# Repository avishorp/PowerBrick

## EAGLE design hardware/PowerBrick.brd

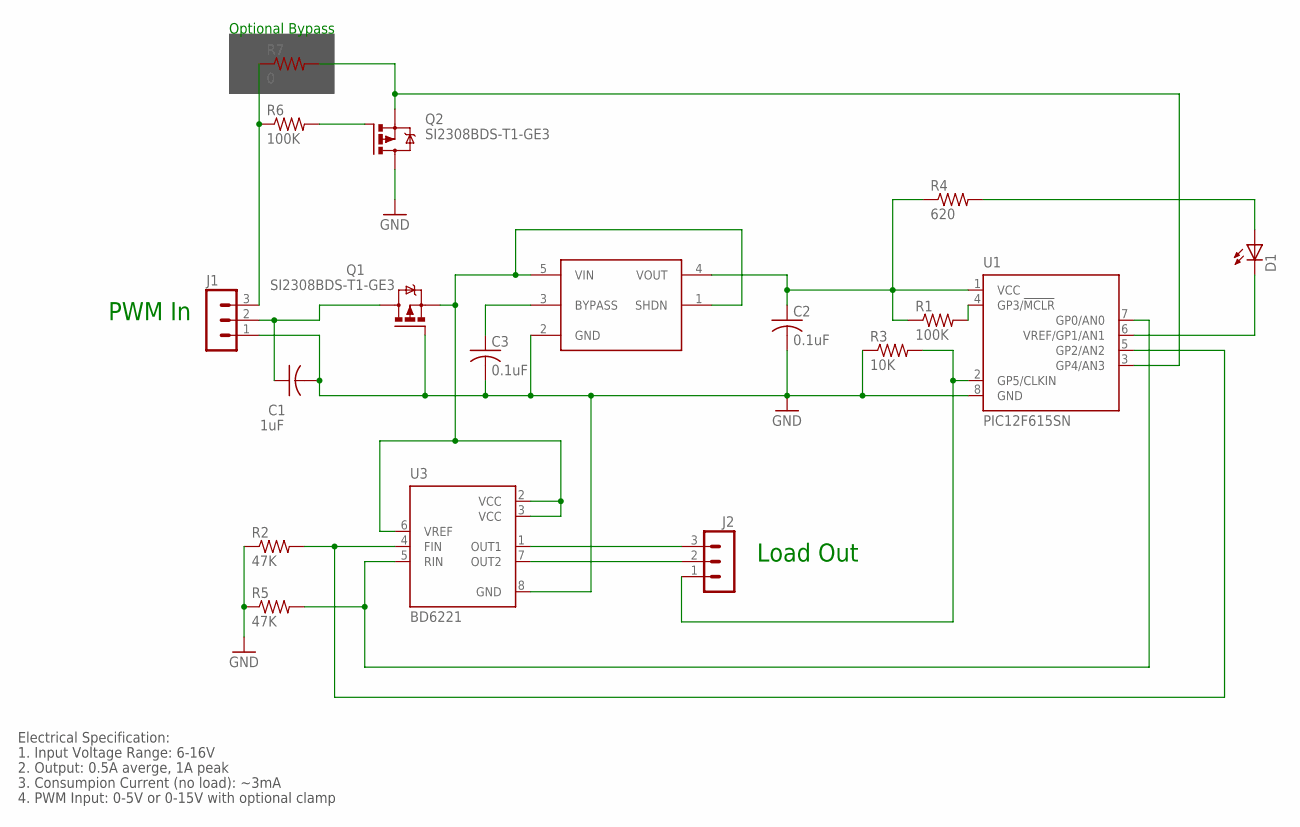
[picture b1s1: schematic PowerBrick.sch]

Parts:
C1: 1uF; C0805
C2, C3: 0.1uF; C0805
D1: LEDCHIPLED_0603; CHIPLED_0603
J1, J2: MA03-1
Q1, Q2: SI2308BDS-T1-GE3; MICRO3
R1, R6: 100K; R0603
R2, R5: 47K; R0603
R3: 10K; R0603
R4: 620; R0603
R7: 0; R0603
U1: PIC12F615SN; SO-08
U2: LK112M50TR; SOT23-5L
U3: BD6221; SOP8

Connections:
GND: C1.2, C2.2, C3.2, J1.1, Q1.1 (G), Q2.3 (D), R2.1, R3.1, R5.1, U1.8 (GND), U2.2 (GND), U3.8 (GND)
J1: Q2.2 (S), R7.2, U1.3 (GP4/AN3)
unnamed: J2.1, R3.2, U1.2 (GP5/CLKIN)
unnamed: Q1.2 (S), U2.1 (SHDN), U2.5 (VIN), U3.2 (VCC), U3.3 (VCC), U3.6 (VREF)
unnamed: C2.1, R1.1, R4.1, U1.1 (VCC), U2.4 (VOUT)
unnamed: J2.3, U3.1 (OUT1)
unnamed: J2.2, U3.7 (OUT2)
unnamed: R2.2, U1.5 (GP2/AN2), U3.4 (FIN)
unnamed: R5.2, U1.7 (GP0/AN0), U3.5 (RIN)
unnamed: D1.A, R4.2
unnamed: D1.C, U1.6 (VREF/GP1/AN1)
unnamed: C1.1, J1.2, Q1.3 (D)
unnamed: R1.2, U1.4 (GP3/!MCLR)
unnamed: Q2.1 (G), R6.2
unnamed: J1.3, R6.1, R7.1
unnamed: C3.1, U2.3 (BYPASS)

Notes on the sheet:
PWM In
Load Out
Optional Bypass
Electrical Specification:
1. Input Voltage Range: 6-16V
2. Output: 0.5A averge, 1A peak
3. Consumpion Current (no load): ~3mA
4. PWM Input: 0-5V or 0-15V with optional clamp

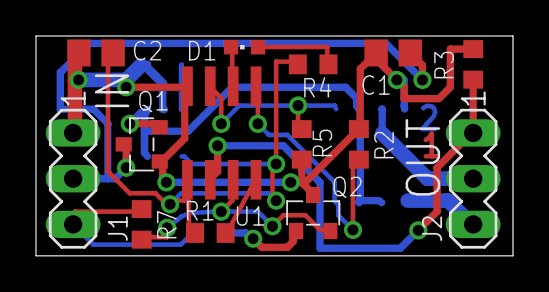
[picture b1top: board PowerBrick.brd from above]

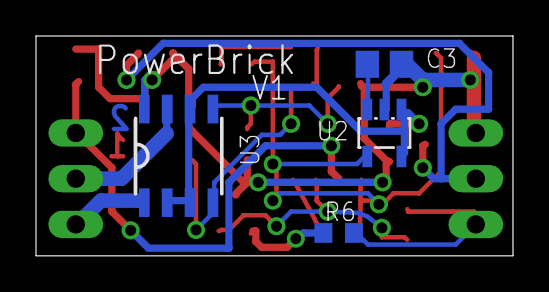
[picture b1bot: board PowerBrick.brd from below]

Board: 2 copper layers, 26.5 x 12.2 mm, 18 parts (4 on the bottom side), 16 nets.

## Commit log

2012-02-02 Initial version, with PIC12F675 (Schematic only)
2012-02-14 * Changed processor * Changed voltage regulator * Added PWM input clamping * Added PCB design
2012-03-04 * Finalized PCB design * Added CAM file generation scripts
2012-03-04 Moved hardware project to a separate directory
2012-06-26 Added optional level shift transistor on the receiver PWM input
2012-06-26 Generated CAM files
2012-06-26 Added firmware project skeleton
2012-06-28 Added some basic functionality (LED and PWM)
2012-06-28 Added bidirectional load drive capability
2012-07-16 Added code implementing most of the software features
